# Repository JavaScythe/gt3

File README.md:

# gt3

High quality DIY 22-input paddle shifted  GT-3 simracing wheel

## Why:
- minimal GT3 format wheel for Logitech G PRO ecosystem, without the squeaking plastic covers and commercial cost cutting.
- reduce awful squeaking noise on high frequency ffb (trueforce) (I can't stress this enough) generated by iRacing
- Easier use for small steering range like Formula Vee
- High quality and stronger paddle shifters.
- Less rotational inertia compared to complete round rims, higher FFB detail

### BOM
|name                         |seller    |cost  |shipping|notes                           |links                                                                                                                                                              |
|-----------------------------|----------|------|--------|--------------------------------|-------------------------------------------------------------------------------------------------------------------------------------------------------------------|
|Adapter                      |logitech  |70    |0       |                                |https://www.logitechg.com/en-us/products/driving/rs-qr-adapter.html                                                                                                |
|CNC total                    |JLCCNC    |178.63|31.72   |                                |                                                                                                                                                                   |
|PCB cost                     |JLCPCB    |5.2   |0       |shipping combined with CNC order|                                                                                                                                                                   |
|Buttons+Spiral+Switch+Magnets|aliexpress|34.66 |0       |                                |aliexpress.us/item/3256809330048515.html aliexpress.us/item/3256805986853569.html aliexpress.us/item/2255800513929044.html aliexpress.us/item/3256804210141616.html|
|Switches+Neopixels           |mouser    |27.55 |9.26    |Includes 1.27 tariff            |https://www.mouser.com/ProductDetail/485-1938 https://www.mouser.com/ProductDetail/653-D2HW-BR213MR                                                                |
|PCBA cost                    |JLCPCB    |33.27 |0       |shipping combined with CNC order|                                                                                                                                                                   |
|Total             |          |349.31|40.98   |390.29                          |

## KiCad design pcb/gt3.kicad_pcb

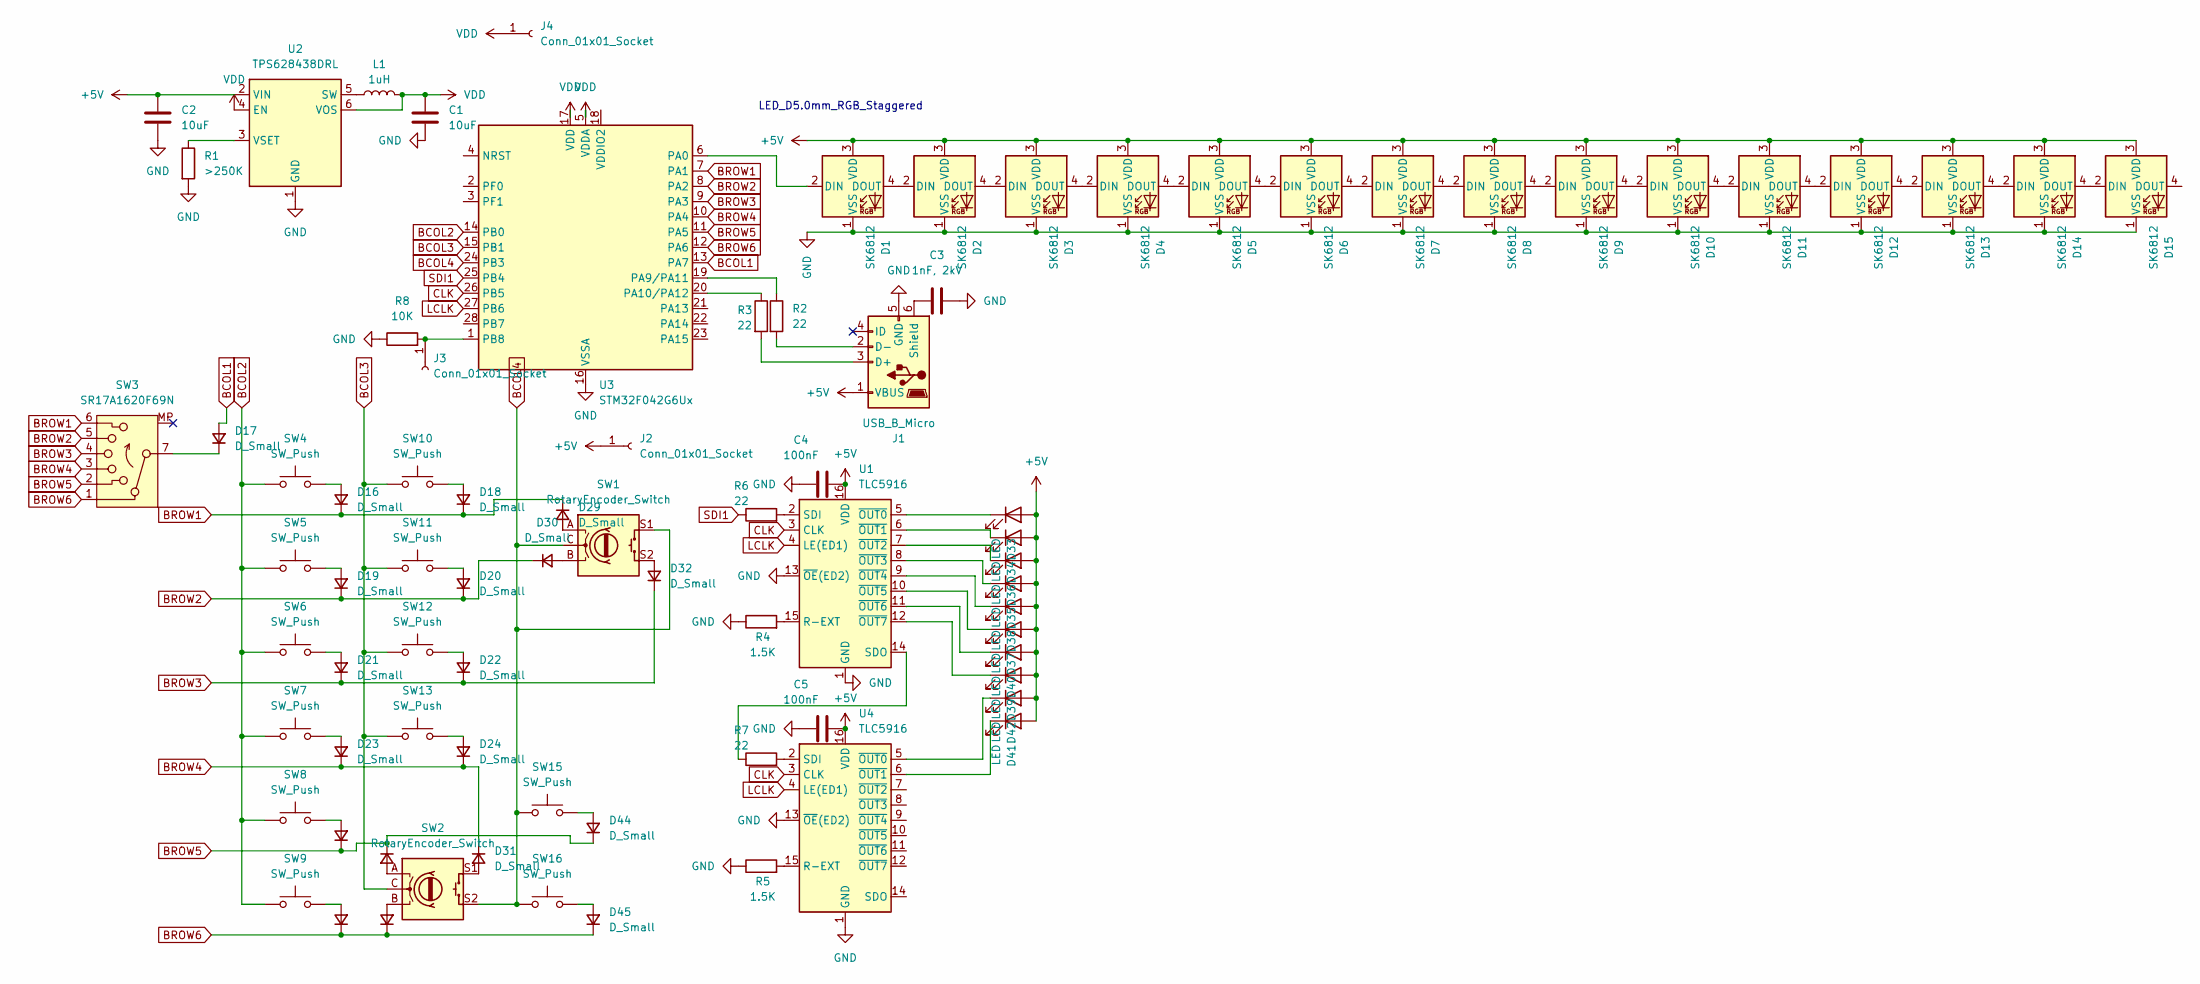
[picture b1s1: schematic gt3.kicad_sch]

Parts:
C1, C2: 10uF; C_0402_1005Metric
C3: 1nF, 2kV; C_1206_3216Metric
C4, C5: 100nF; C_0402_1005Metric
D1, D2, D3, D4, D5, D6, D7, D8, D9, D10, D11, D12, D13, D14, D15: SK6812; LED_D5.0mm-4_RGB_Staggered_Pins_FIX
D16, D17, D18, D19, D20, D21, D22, D23, D24, D25, D26, D27, D28, D29, D30, D31, D32, D44, D45: D_Small; D_0402_1005Metric-Model
D33, D34, D35, D36, D37, D38, D39, D40, D41, D42: LED; SolderWire-0.1sqmm_1x01_D0.4mm_OD1mm
J1: USB_B_Micro; USB_Micro-AB_Molex_47590-0001
J2: Conn_01x01_Socket; TerminalBlock_MetzConnect_360272_1x01_Horizontal_ScrewM2.6
J3, J4: Conn_01x01_Socket; TestPoint_Pad_1.0x1.0mm
L1: 1uH; L_0805_2012Metric
R1: >250K; R_0402_1005Metric
R2, R3, R6, R7: 22; R_0402_1005Metric
R4, R5: 1.5K; R_0603_1608Metric
R8: 10K; R_0402_1005Metric
SW1, SW2: RotaryEncoder_Switch; 1X05PliggleBopFonemeWire
SW3: SR17A1620F69N; 1X07PliggleBopFonemeWire
SW4, SW5, SW6, SW7, SW8, SW9, SW10, SW11, SW12, SW13, SW15, SW16: SW_Push; SolderWire-0.1sqmm_1x02_P3.6mm_D0.4mm_OD1mm
U1, U4: TLC5916; SOIC127P600X175-16N
U2: TPS628438DRL; SOT-563
U3: STM32F042G6Ux; STM32F042G6U

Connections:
+5V: C2.2, C4.2, C5.2, D1.3 (VDD), D2.3 (VDD), D3.3 (VDD), D4.3 (VDD), D5.3 (VDD), D6.3 (VDD), D7.3 (VDD), D8.3 (VDD), D9.3 (VDD), D10.3 (VDD), D11.3 (VDD), D12.3 (VDD), D13.3 (VDD), D14.3 (VDD), D15.3 (VDD), D33.2 (A), D34.2 (A), D35.2 (A), D36.2 (A), D37.2 (A), D38.2 (A), D39.2 (A), D40.2 (A), D41.2 (A), D42.2 (A), J1.1 (VBUS), J2.1, U1.16 (VDD), U2.2 (VIN), U4.16 (VDD)
BCOL1: D17.2 (A), U3.13 (PA7)
BCOL2: SW4.1, SW5.1, SW6.1, SW7.1, SW8.1, SW9.1, U3.14 (PB0)
BCOL3: SW2.C, SW10.1, SW11.1, SW12.1, SW13.1, U3.15 (PB1)
BCOL4: SW1.C, SW1.S1, SW2.S2, SW15.1, SW16.1, U3.24 (PB3)
BROW1: D16.1 (K), D18.1 (K), D29.1 (K), SW3.6, U3.7 (PA1)
BROW2: D19.1 (K), D20.1 (K), D30.1 (K), SW3.5, U3.8 (PA2)
BROW3: D21.1 (K), D22.1 (K), D32.1 (K), SW3.4, U3.9 (PA3)
BROW4: D23.1 (K), D24.1 (K), D31.1 (K), SW3.3, U3.10 (PA4)
BROW5: D25.1 (K), D26.1 (K), D44.1 (K), SW3.2, U3.11 (PA5)
BROW6: D27.1 (K), D28.1 (K), D45.1 (K), SW3.1, U3.12 (PA6)
CLK: U1.3 (CLK), U3.26 (PB5), U4.3 (CLK)
GND: C1.2, C2.1, C3.2, C4.1, C5.1, D1.1 (VSS), D2.1 (VSS), D3.1 (VSS), D4.1 (VSS), D5.1 (VSS), D6.1 (VSS), D7.1 (VSS), D8.1 (VSS), D9.1 (VSS), D10.1 (VSS), D11.1 (VSS), D12.1 (VSS), D13.1 (VSS), D14.1 (VSS), D15.1 (VSS), J1.5 (GND), R1.2, R4.1, R5.1, R8.1, U1.1 (GND), U1.13 (~OE(ED2)), U2.1 (GND), U3.16 (VSSA), U4.1 (GND), U4.13 (~OE(ED2))
LCLK: U1.4 (LE(ED1)), U3.27 (PB6), U4.4 (LE(ED1))
unnamed: D1.2 (DIN), U3.6 (PA0)
unnamed: D1.4 (DOUT), D2.2 (DIN)
unnamed: D2.4 (DOUT), D3.2 (DIN)
unnamed: D3.4 (DOUT), D4.2 (DIN)
unnamed: D4.4 (DOUT), D5.2 (DIN)
unnamed: D5.4 (DOUT), D6.2 (DIN)
unnamed: D6.4 (DOUT), D7.2 (DIN)
unnamed: D7.4 (DOUT), D8.2 (DIN)
unnamed: D8.4 (DOUT), D9.2 (DIN)
unnamed: D9.4 (DOUT), D10.2 (DIN)
unnamed: D10.4 (DOUT), D11.2 (DIN)
unnamed: D11.4 (DOUT), D12.2 (DIN)
unnamed: D12.4 (DOUT), D13.2 (DIN)
unnamed: D13.4 (DOUT), D14.2 (DIN)
unnamed: D14.4 (DOUT), D15.2 (DIN)
unnamed: D16.2 (A), SW4.2
unnamed: D17.1 (K), SW3.7
unnamed: D18.2 (A), SW10.2
unnamed: D19.2 (A), SW5.2
unnamed: D20.2 (A), SW11.2
unnamed: D21.2 (A), SW6.2
unnamed: D22.2 (A), SW12.2
unnamed: D23.2 (A), SW7.2
unnamed: D24.2 (A), SW13.2
unnamed: D25.2 (A), SW8.2
unnamed: D26.2 (A), SW2.A
unnamed: D27.2 (A), SW9.2
unnamed: D28.2 (A), SW2.B
unnamed: D29.2 (A), SW1.A
unnamed: D30.2 (A), SW1.B
unnamed: D31.2 (A), SW2.S1
unnamed: D32.2 (A), SW1.S2
unnamed: D33.1 (K), U1.5 (~OUT0)
unnamed: D34.1 (K), U1.6 (~OUT1)
unnamed: D35.1 (K), U1.8 (~OUT3)
unnamed: D36.1 (K), U1.7 (~OUT2)
unnamed: D37.1 (K), U1.10 (~OUT5)
unnamed: D38.1 (K), U1.9 (~OUT4)
unnamed: D39.1 (K), U1.12 (~OUT7)
unnamed: D40.1 (K), U1.11 (~OUT6)
unnamed: D41.1 (K), U4.6 (~OUT1)
unnamed: D42.1 (K), U4.5 (~OUT0)
unnamed: D44.2 (A), SW15.2
unnamed: D45.2 (A), SW16.2
unnamed: J1.3 (D+), R3.2
unnamed: J1.2 (D-), R2.2
unnamed: C3.1, J1.6 (Shield)
unnamed 61: J3.1, R8.2, U3.1 (PB8); also elsewhere on the board
unnamed: R4.2, U1.15 (R-EXT)
unnamed: R6.2, U1.2 (SDI)
unnamed: R7.1, U1.14 (SDO)
unnamed: L1.1, U2.5 (SW)
unnamed: R1.1, U2.3 (VSET)
unnamed: R2.1, U3.19 (PA9/PA11)
unnamed: R3.1, U3.20 (PA10/PA12)
unnamed: R5.2, U4.15 (R-EXT)
unnamed: R7.2, U4.2 (SDI)
SDI1: R6.1, U3.25 (PB4)
VDD: C1.1, J4.1, L1.2, U2.4 (EN), U2.6 (VOS), U3.5 (VDDA), U3.17 (VDD); also elsewhere on the board

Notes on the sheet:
LED_D5.0mm_RGB_Staggered

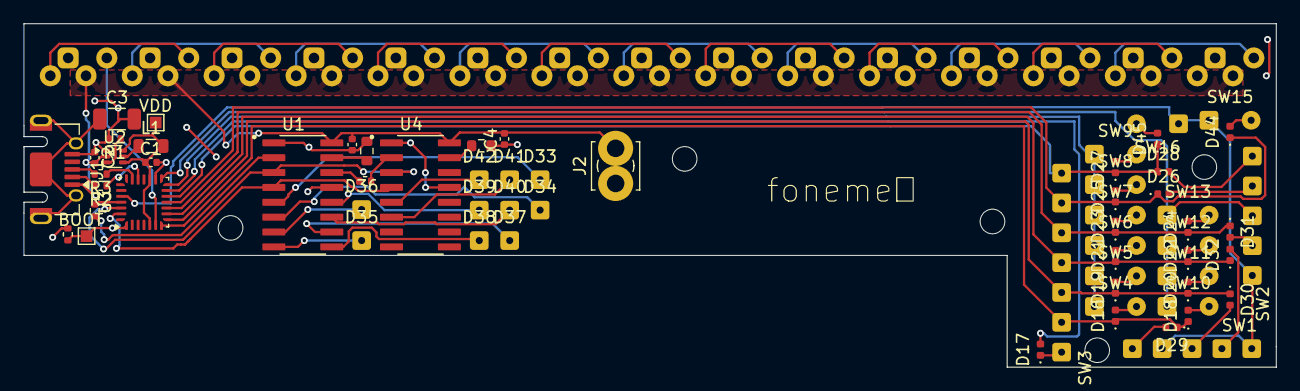
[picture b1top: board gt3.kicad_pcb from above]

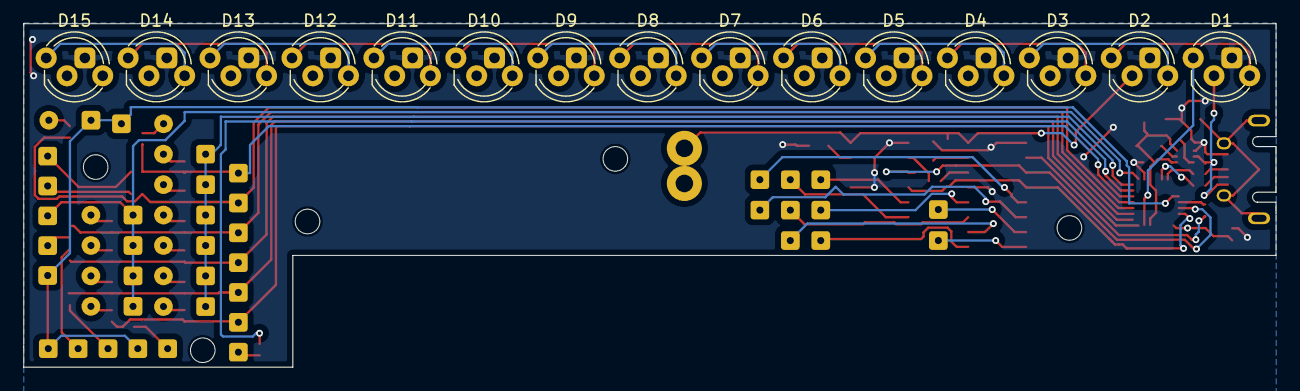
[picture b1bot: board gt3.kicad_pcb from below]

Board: 2 copper layers, 107.0 x 29.3 mm, 81 parts (15 on the bottom side), 73 nets.

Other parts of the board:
BOOT: Conn_01x01_Socket; TestPoint_Pad_1.0x1.0mm
VDD: Conn_01x01_Socket; TestPoint_Pad_1.0x1.0mm

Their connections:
unnamed 61: BOOT.1; also elsewhere on the board
VDD: VDD.1; also elsewhere on the board

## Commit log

2025-07-29 Update from local
2025-07-29 upload minor things
